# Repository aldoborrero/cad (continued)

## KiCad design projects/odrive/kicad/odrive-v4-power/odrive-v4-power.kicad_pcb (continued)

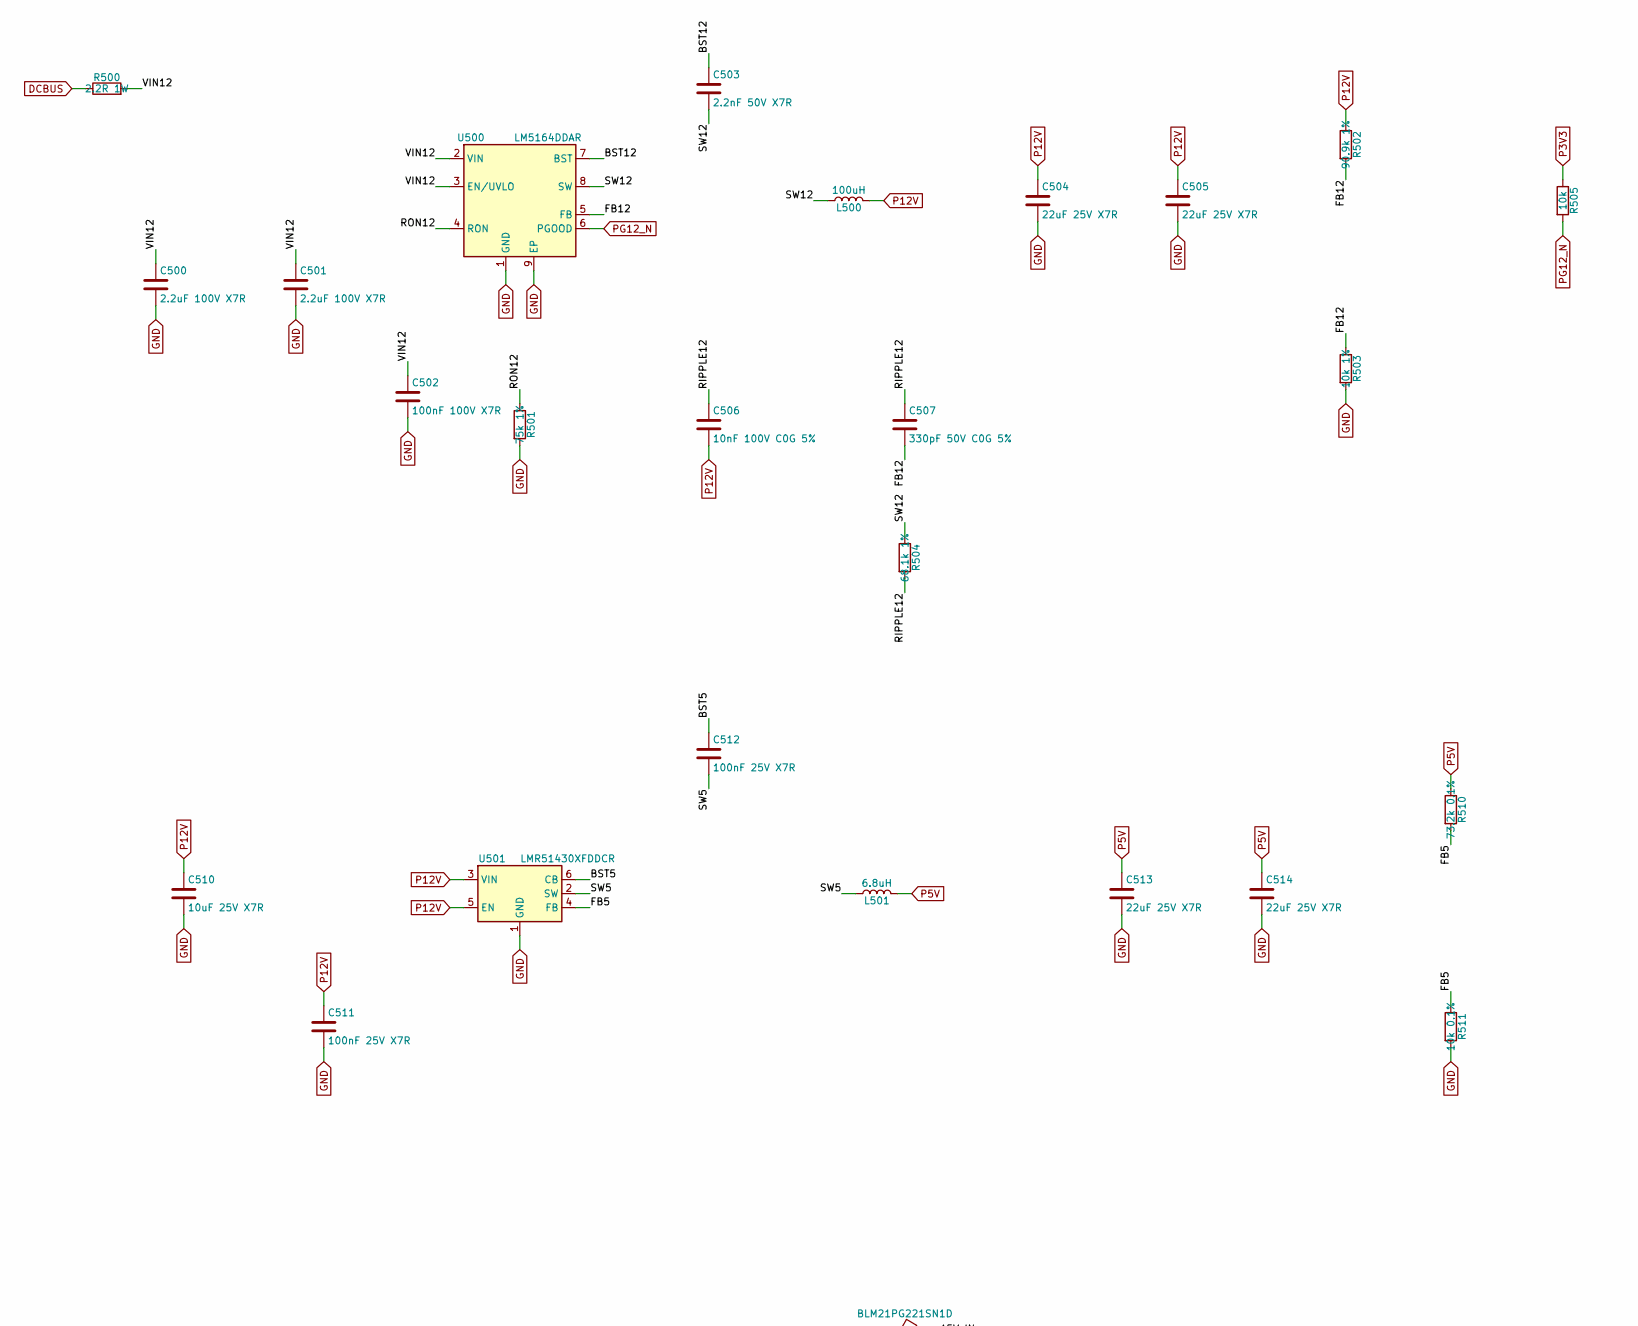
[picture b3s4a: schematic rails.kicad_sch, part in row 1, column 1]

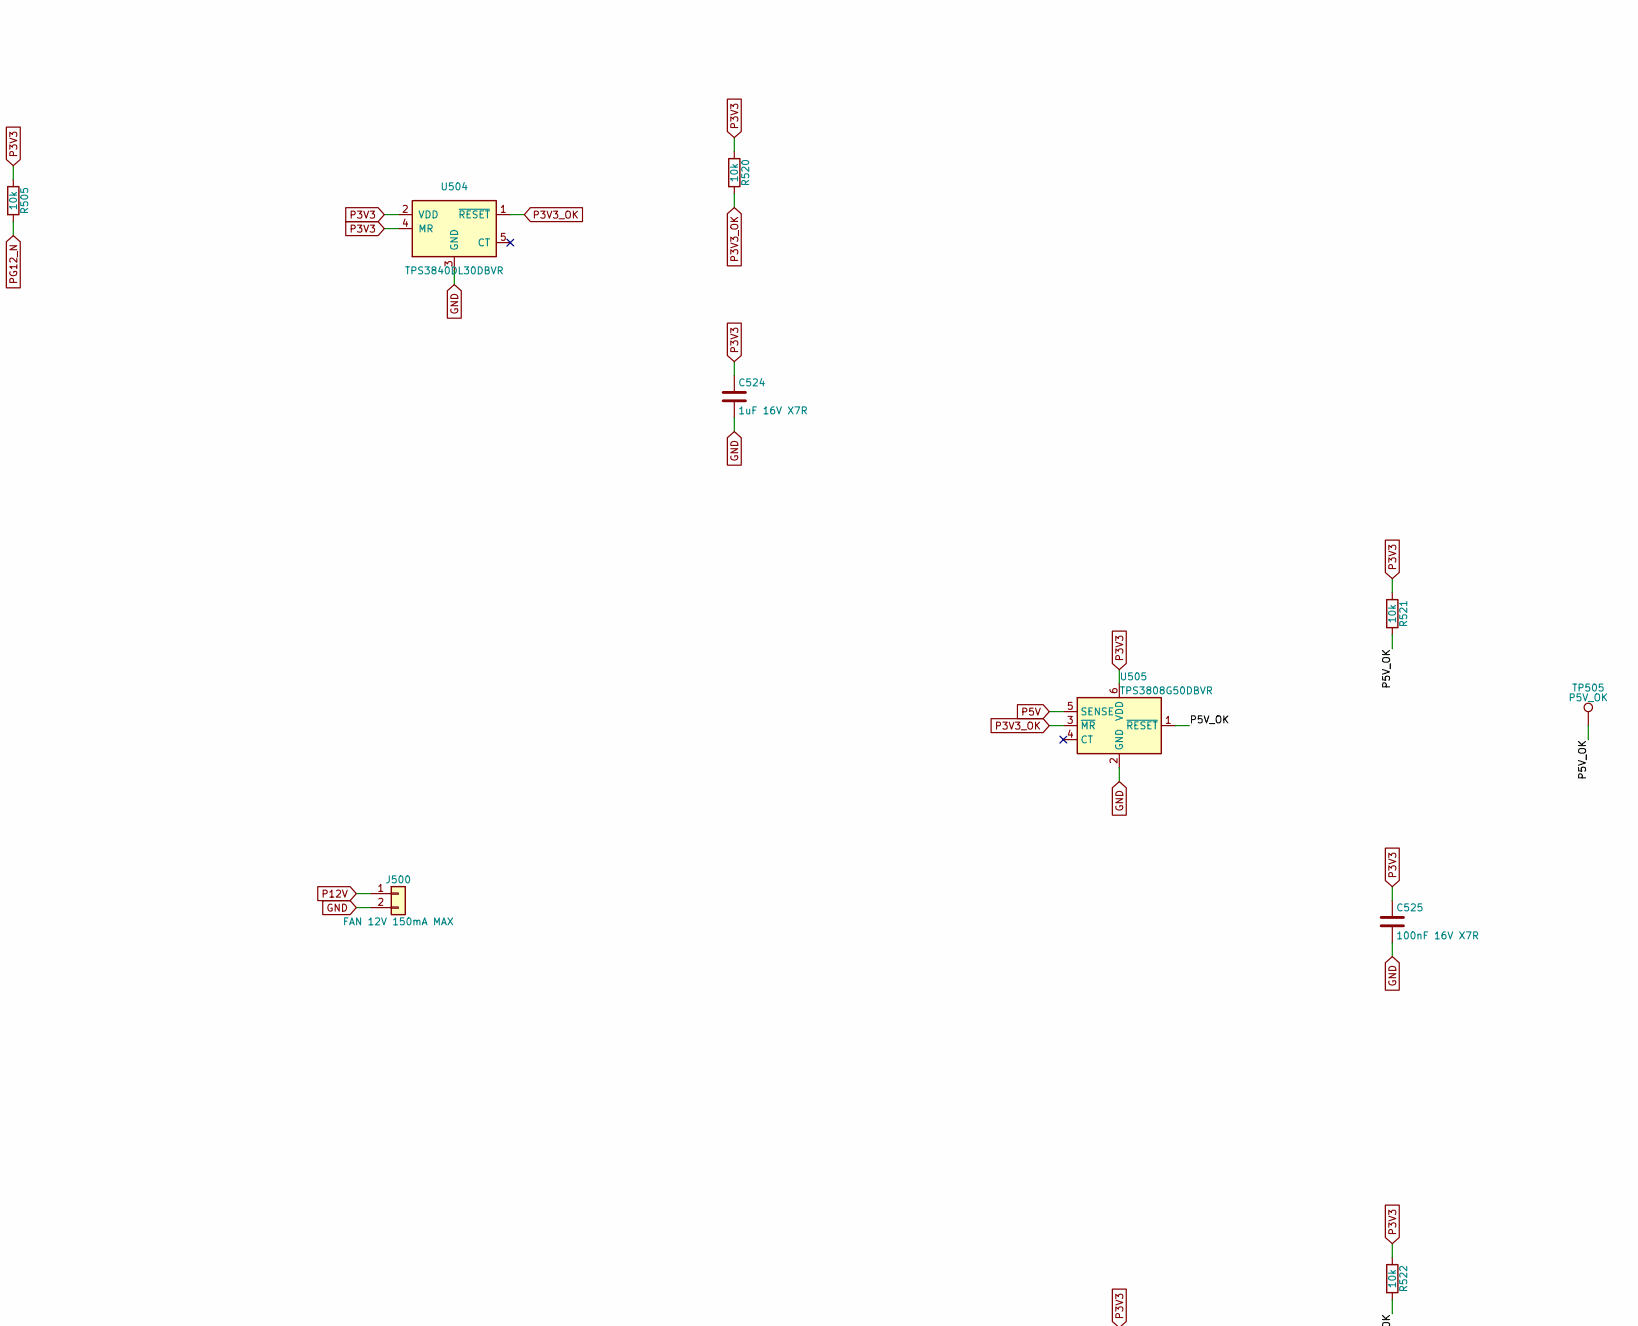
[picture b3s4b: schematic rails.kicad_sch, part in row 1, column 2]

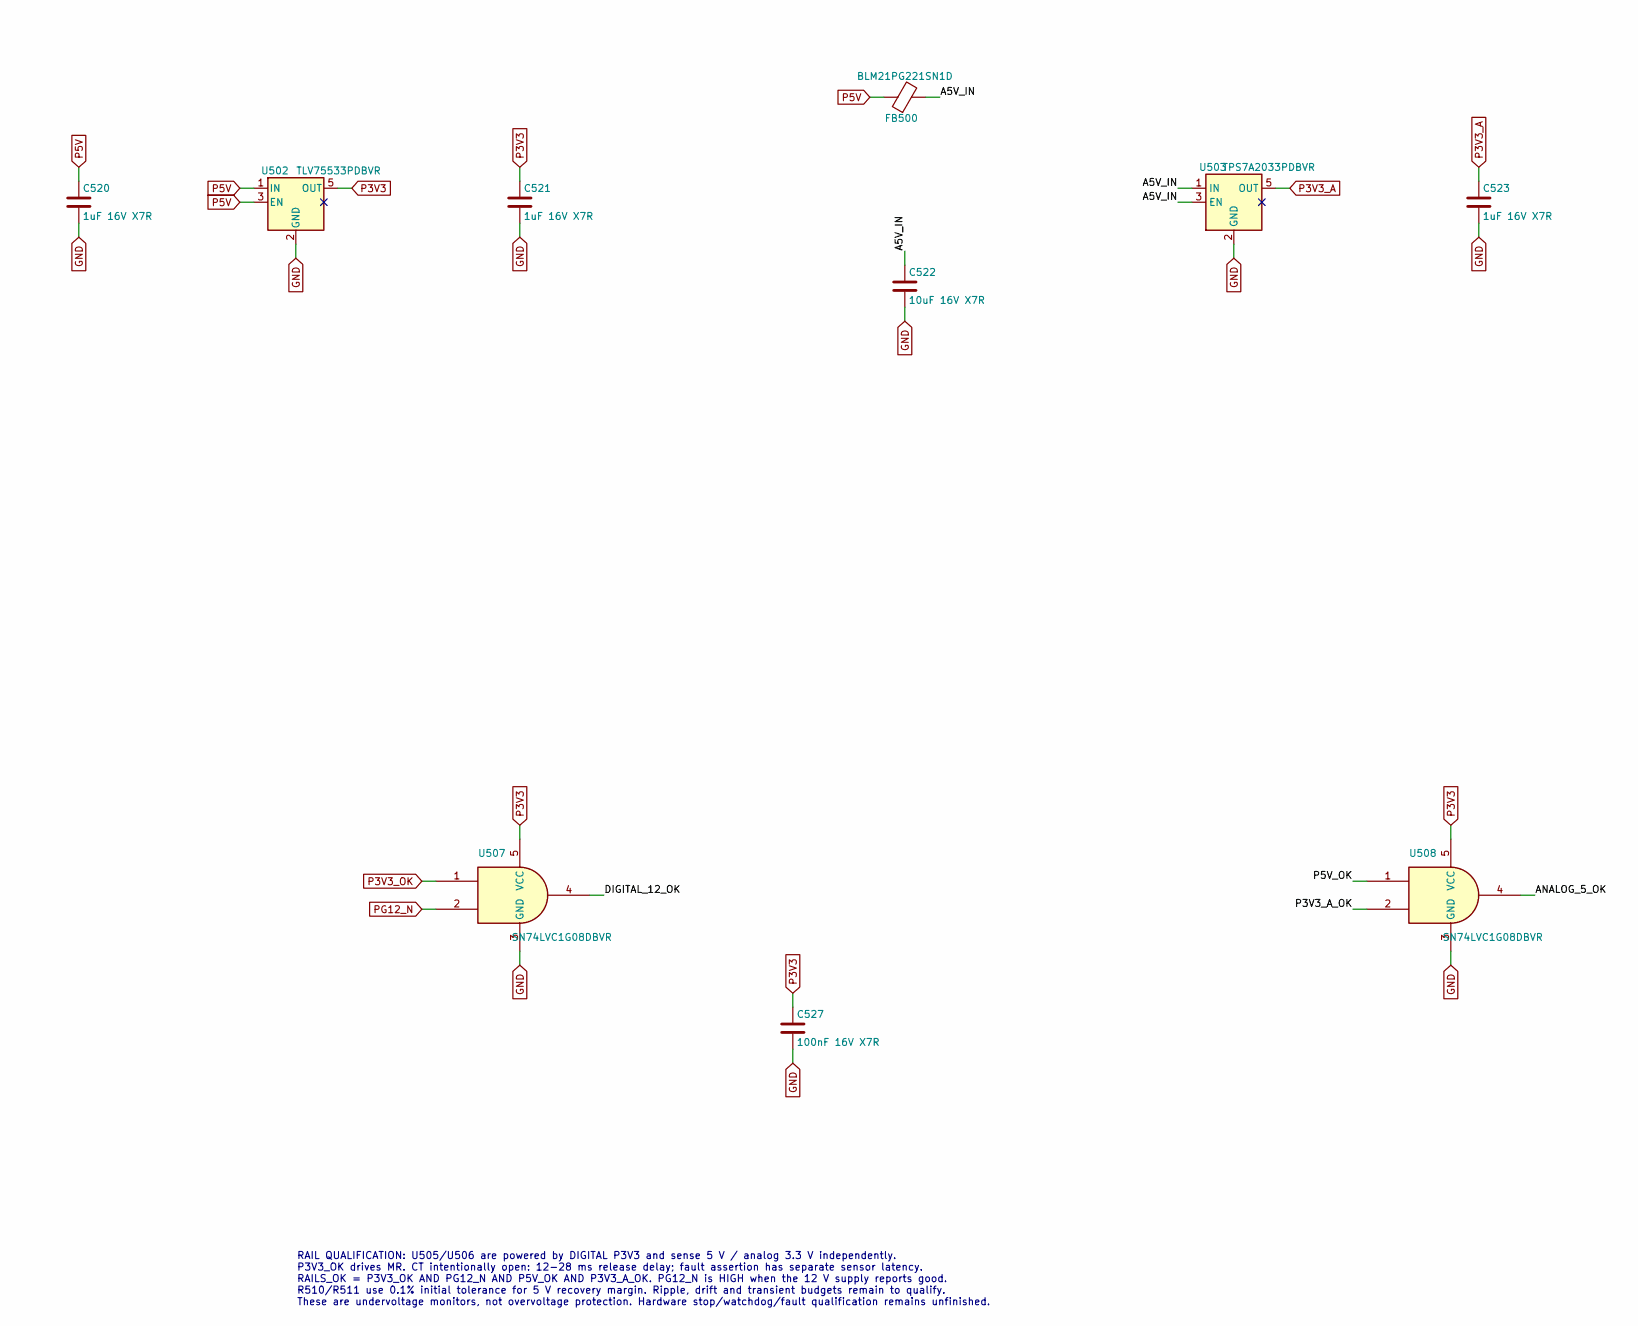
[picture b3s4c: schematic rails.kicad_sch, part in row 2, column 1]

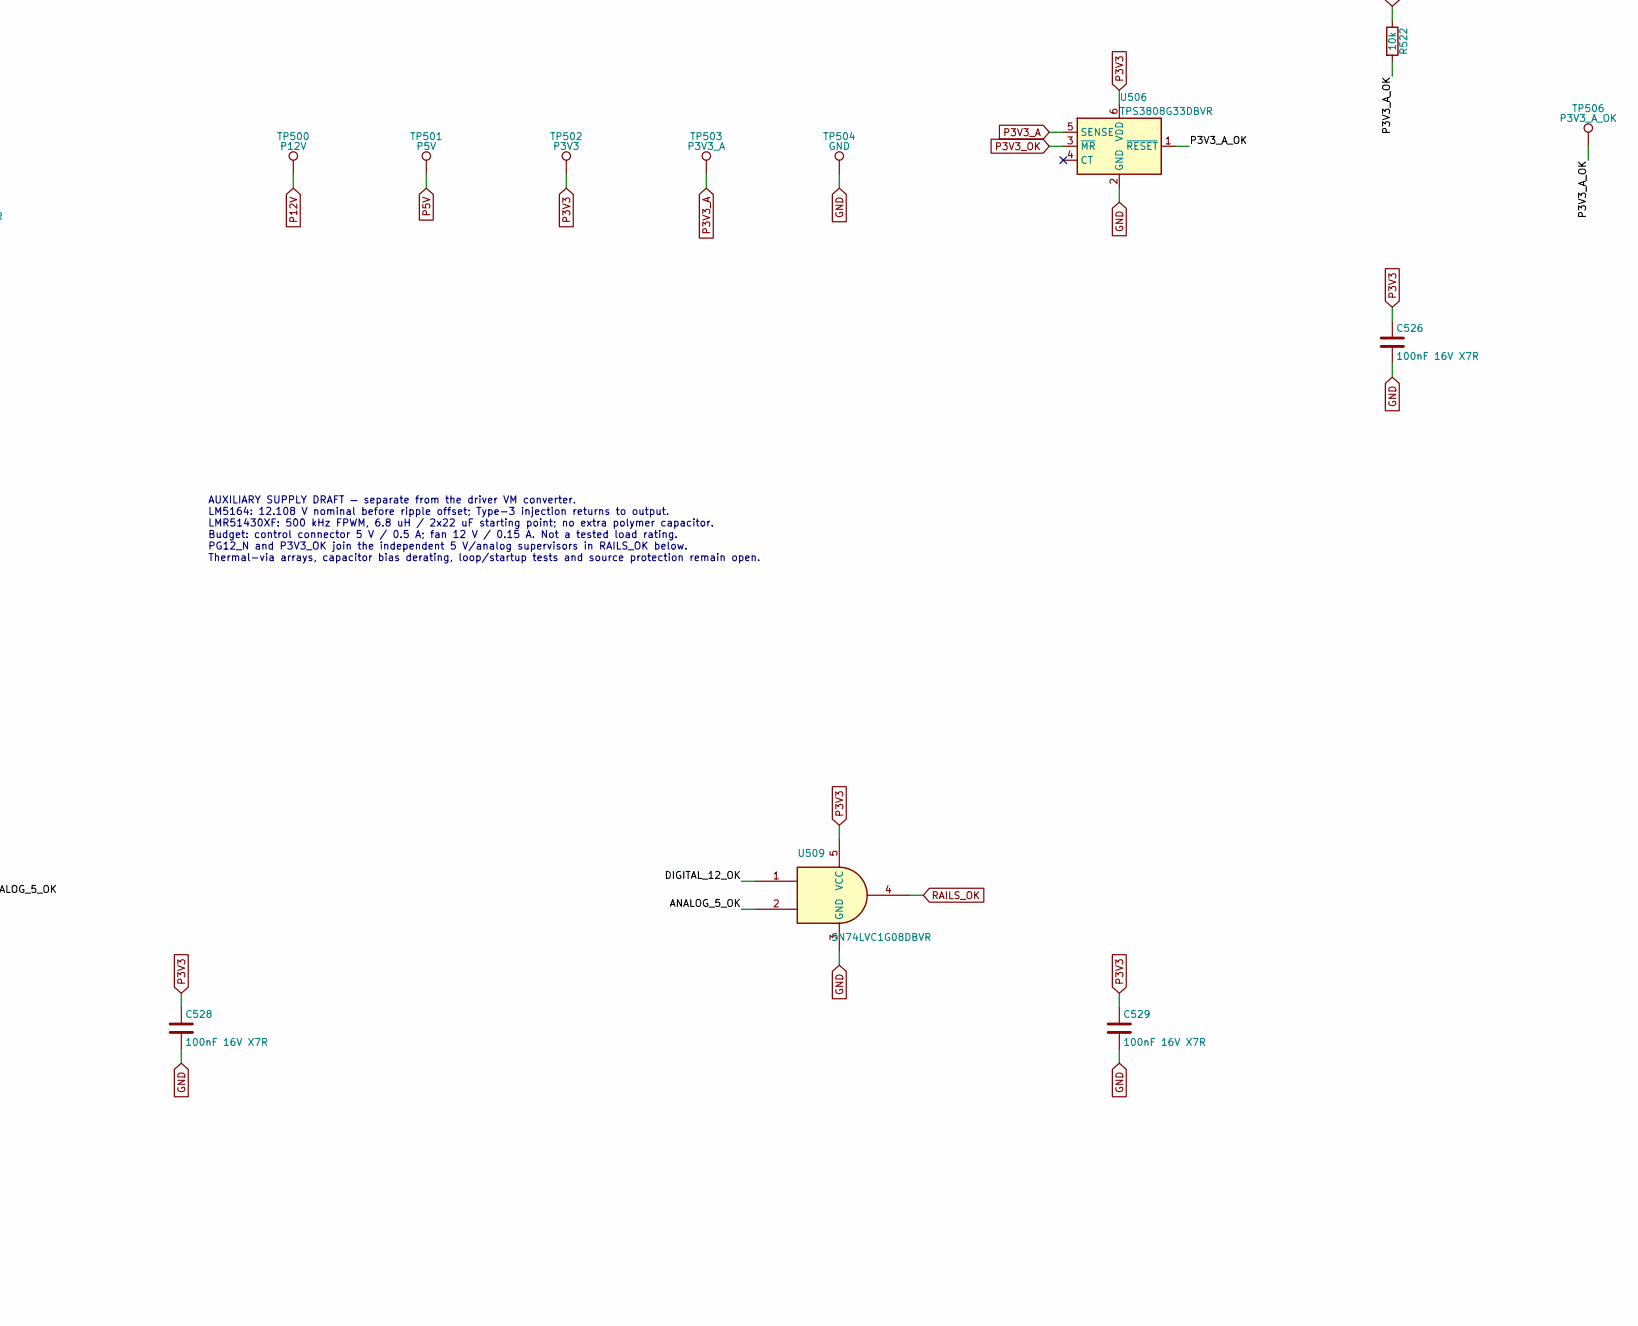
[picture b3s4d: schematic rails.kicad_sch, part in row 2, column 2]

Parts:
C500, C501: 2.2uF 100V X7R; C_1210_3225Metric
C502: 100nF 100V X7R; C_0603_1608Metric
C503: 2.2nF 50V X7R; C_0603_1608Metric
C504, C505, C513, C514: 22uF 25V X7R; C_1210_3225Metric
C506: 10nF 100V C0G 5%; C_0603_1608Metric
C507: 330pF 50V C0G 5%; C_0603_1608Metric
C510: 10uF 25V X7R; C_0805_2012Metric
C511, C512: 100nF 25V X7R; C_0603_1608Metric
C520, C521, C523, C524: 1uF 16V X7R; C_0603_1608Metric
C522: 10uF 16V X7R; C_0805_2012Metric
C525, C526, C527, C528, C529: 100nF 16V X7R; C_0603_1608Metric
FB500: BLM21PG221SN1D; L_0805_2012Metric
J500: FAN 12V 150mA MAX; PinHeader_1x02_P2.54mm_Vertical
L500: 100uH; L_Wuerth_WE-PD-Typ-LS
L501: 6.8uH; Coilcraft_XAL7070_682
R500: 2.2R 1W; R_2512_6332Metric
R501: 75k 1%; R_0603_1608Metric
R502: 90.9k 1%; R_0603_1608Metric
R503: 10k 1%; R_0603_1608Metric
R504: 68.1k 1%; R_0805_2012Metric
R505, R520, R521, R522: 10k; R_0603_1608Metric
R510: 73.2k 0.1%; R_0603_1608Metric
R511: 10k 0.1%; R_0603_1608Metric
TP500: P12V; TestPoint_Pad_D1.0mm
TP501: P5V; TestPoint_Pad_D1.0mm
TP502: P3V3; TestPoint_Pad_D1.0mm
TP503: P3V3_A; TestPoint_Pad_D1.0mm
TP504: GND; TestPoint_Pad_D1.0mm
TP505: P5V_OK; TestPoint_Pad_D1.0mm
TP506: P3V3_A_OK; TestPoint_Pad_D1.0mm
U500: LM5164DDAR; HSOP-8-1EP_3.9x4.9mm_P1.27mm_EP2.41x3.1mm
U501: LMR51430XFDDCR; TI_DDC0006A
U502: TLV75533PDBVR; SOT-23-5
U503: TPS7A2033PDBVR; SOT-23-5
U504: TPS3840DL30DBVR; SOT-23-5
U505: TPS3808G50DBVR; SOT-23-6
U506: TPS3808G33DBVR; SOT-23-6
U507, U508, U509: SN74LVC1G08DBVR; SOT-23-5

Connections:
/Auxiliary rails/A5V_IN: C522.1, FB500.2, U503.1 (IN), U503.3 (EN)
/Auxiliary rails/ANALOG_5_OK: U508.4, U509.2
/Auxiliary rails/BST5: C512.1, U501.6 (CB)
/Auxiliary rails/BST12: C503.1, U500.7 (BST)
/Auxiliary rails/DIGITAL_12_OK: U507.4, U509.1
/Auxiliary rails/FB5: R510.2, R511.1, U501.4 (FB)
/Auxiliary rails/FB12: C507.2, R502.2, R503.1, U500.5 (FB)
/Auxiliary rails/P3V3_A_OK: R522.2, TP506.1, U506.1 (~RESET), U508.2
/Auxiliary rails/P5V_OK: R521.2, TP505.1, U505.1 (~RESET), U508.1
/Auxiliary rails/RIPPLE12: C506.1, C507.1, R504.2
/Auxiliary rails/RON12: R501.1, U500.4 (RON)
/Auxiliary rails/SW5: C512.2, L501.1, U501.2 (SW)
/Auxiliary rails/SW12: C503.2, L500.1, R504.1, U500.8 (SW)
/Auxiliary rails/VIN12: C500.1, C501.1, C502.1, R500.2, U500.2 (VIN), U500.3 (EN/UVLO)
DCBUS: R500.1; also elsewhere on the board
GND: C500.2, C501.2, C502.2, C504.2, C505.2, C510.2, C511.2, C513.2, C514.2, C520.2, C521.2, C522.2, C523.2, C524.2, C525.2, C526.2, C527.2, C528.2, C529.2, J500.2, R501.2, R503.2, R511.2, TP504.1, U500.1 (GND), U500.9 (EP), U501.1 (GND), U502.2 (GND), U503.2 (GND), U504.3 (GND), U505.2 (GND), U506.2 (GND), U507.3 (GND), U508.3 (GND), U509.3 (GND); also elsewhere on the board
P3V3: C521.1, C524.1, C525.1, C526.1, C527.1, C528.1, C529.1, R505.1, R520.1, R521.1, R522.1, TP502.1, U502.5 (OUT), U504.2 (VDD), U504.4 (MR), U505.6 (VDD), U506.6 (VDD), U507.5 (VCC), U508.5 (VCC), U509.5 (VCC); also elsewhere on the board
P3V3_A: C523.1, TP503.1, U503.5 (OUT), U506.5 (SENSE); also elsewhere on the board
P3V3_OK: R520.2, U504.1 (~RESET), U505.3 (~MR), U506.3 (~MR), U507.1; also elsewhere on the board
P5V: C513.1, C514.1, C520.1, FB500.1, L501.2, R510.1, TP501.1, U502.1 (IN), U502.3 (EN), U505.5 (SENSE); also elsewhere on the board
P12V: C504.1, C505.1, C506.2, C510.1, C511.1, J500.1, L500.2, R502.1, TP500.1, U501.3 (VIN), U501.5 (EN)
PG12_N: R505.2, U500.6 (PGOOD), U507.2
RAILS_OK: U509.4; also elsewhere on the board

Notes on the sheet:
RAIL QUALIFICATION: U505/U506 are powered by DIGITAL P3V3 and sense 5 V / analog 3.3 V independently. P3V3_OK drives MR. CT intentionally open: 12-28 ms release delay; fault assertion has separate sensor latency. RAILS_OK = P3V3_OK AND PG12_N AND P5V_OK AND P3V3_A_OK. PG12_N is HIGH when the 12 V s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
AUXILIARY SUPPLY DRAFT — separate from the driver VM converter. LM5164: 12.108 V nominal before ripple offset; Type-3 injection returns to output. LMR51430XF: 500 kHz FPWM, 6.8 uH / 2x22 uF starting point; no extra polymer capacitor. Budget: control connector 5 V / 0.5 A; fan 12 V / 0.15 A. Not a t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

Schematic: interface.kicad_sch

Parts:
C600, C601, C602, C603, C604, C605, C610, C611, C612, C613, C614, C615, C616, C620, C621, C622, C623, C624, C625, C640, C642, C643, C644, C645, C646, C647, C648, C649, C650, C651, C652, C653, C654, C655, C656: 100nF 16V X7R; C_0603_1608Metric
C630, C631, C632, C641: 47pF 50V C0G 5%; C_0603_1608Metric
J600: STOP NC LOOP; PhoenixContact_MSTBA_2,5_2-G-5,08_1x02_P5.08mm_Horizontal
R600, R601, R602, R603, R604, R605, R610, R615, R617, R636, R650: 1k; R_0603_1608Metric
R611, R612, R613, R614, R616, R618, R619, R620, R621, R622, R623, R624, R625, R626, R627, R632, R635, R637, R638, R639, R640, R641, R651, R652, R659, R660, R661, R662, R663, R664, R676: 10k; R_0603_1608Metric
R630, R631, R633, R634: 220R 1%; R_0603_1608Metric
R653, R656: 100k 0.1%; R_0603_1608Metric
R654, R657, R671, R674: 976k 1%; R_0603_1608Metric
R655, R658: 182k 1%; R_0603_1608Metric
R670, R673: 169k 0.1%; R_0603_1608Metric
R672, R675: 102k 1%; R_0603_1608Metric
TP600: ARM_STORED; TestPoint_Pad_D1.0mm
TP601: MOTOR_PERMISSION; TestPoint_Pad_D1.0mm
TP602: DRV_ENABLE; TestPoint_Pad_D1.0mm
TP603: STOP_OK; TestPoint_Pad_D1.0mm
TP604: PRESENCE_OK; TestPoint_Pad_D1.0mm
TP605: WD_RECENT; TestPoint_Pad_D1.0mm
TP606: WD_OK; TestPoint_Pad_D1.0mm
U600, U601, U602, U603, U604, U605, U611, U612, U613, U615, U616, U623, U624, U625, U634, U635, U644: SN74LVC1G08DBVR; SOT-23-5
U610, U638, U639: SN74LVC1G74DCUR; TI_DCU0008A
U614, U620, U621, U622, U630: SN74LVC1G17DBVR; SOT-23-5
U631: LTC6993HS6-2#TRPBF; TSOT-23-6
U632: LTC6993HS6-4#TRPBF; TSOT-23-6
U633, U641, U643: SN74LVC1G32DBVR; SOT-23-5
U636: LTC6993HS6-1#TRPBF; TSOT-23-6
U637: LTC6993HS6-3#TRPBF; TSOT-23-6
U640, U642, U645: SN74LVC1G04DBVR; SOT-23-5

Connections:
/Interface and hardware interlocks/ARM_CORE_READY: R626.1, U615.1, U635.4
/Interface and hardware interlocks/ARM_FB_DRIVE: R617.1, R618.1, U614.4
/Interface and hardware interlocks/ARM_READY: R613.1, U610.6 (~CLR), U612.2, U615.4
/Interface and hardware interlocks/ARM_REQ: R610.2, R611.1, U610.1 (C), U611.2, U645.2
/Interface and hardware interlocks/ARM_REQUEST_HELD: U611.4, U612.1
/Interface and hardware interlocks/ARM_STORED: R619.1, TP600.1, U610.5 (Q), U611.1
/Interface and hardware interlocks/CTRL_ALIVE_OK: R640.1, U622.4, U624.2
/Interface and hardware interlocks/CTRL_ALIVE_SENSE: C632.1, R636.2, R637.1, U622.2
/Interface and hardware interlocks/DRV_WAKE_REQ: R615.2, R616.1, U613.1
/Interface and hardware interlocks/MOTOR_PERMISSION: R612.1, TP601.1, U600.2, U601.2, U602.2, U603.2, U604.2, U605.2, U612.4, U614.2
/Interface and hardware interlocks/PRESENCE_OK: R639.1, TP604.1, U621.4, U623.2
/Interface and hardware interlocks/PRESENCE_SENSE: C631.1, R634.2, R635.1, U621.2
/Interface and hardware interlocks/PWM_AH_IN: R600.2, R620.1, U600.1
/Interface and hardware interlocks/PWM_AL_IN: R601.2, R621.1, U601.1
/Interface and hardware interlocks/PWM_BH_IN: R602.2, R622.1, U602.1
/Interface and hardware interlocks/PWM_BL_IN: R603.2, R623.1, U603.1
/Interface and hardware interlocks/PWM_CH_IN: R604.2, R624.1, U604.1
/Interface and hardware interlocks/PWM_CL_IN: R605.2, R625.1, U605.1
/Interface and hardware interlocks/STOP_OK: R638.1, TP603.1, U620.4, U623.1
/Interface and hardware interlocks/STOP_PRESENCE_OK: U623.4, U624.1
/Interface and hardware interlocks/STOP_RETURN: J600.2, R631.1
/Interface and hardware interlocks/STOP_SEND: J600.1, R630.2
/Interface and hardware interlocks/STOP_SENSE: C630.1, R631.2, R632.1, U620.2
/Interface and hardware interlocks/WAKE_CONDITIONS_OK: R627.1, U625.4, U644.1
/Interface and hardware interlocks/WAKE_READY: R614.1, U613.2, U616.4
/Interface and hardware interlocks/WAKE_WITH_WD: U616.2, U644.4
/Interface and hardware interlocks/WD_EARLY: U641.4, U642.2
/Interface and hardware interlocks/WD_EARLY_FALL: R664.1, U639.5 (Q), U641.2
/Interface and hardware interlocks/WD_EARLY_FALL_T_DIV: R674.2, R675.1, U637.4 (DIV)
/Interface and hardware interlocks/WD_EARLY_FALL_T_SET: R673.1, U637.3 (SET)
/Interface and hardware interlocks/WD_EARLY_RISE: R663.1, U638.5 (Q), U641.1
/Interface and hardware interlocks/WD_EARLY_RISE_T_DIV: R671.2, R672.1, U636.4 (DIV)
/Interface and hardware interlocks/WD_EARLY_RISE_T_SET: R670.1, U636.3 (SET)
/Interface and hardware interlocks/WD_FALL_ACTIVE: U632.6 (OUT), U633.2
/Interface and hardware interlocks/WD_INV: U639.1 (C), U640.4
/Interface and hardware interlocks/WD_LATE_FALL_DIV: R657.2, R658.1, U632.4 (DIV)
/Interface and hardware interlocks/WD_LATE_FALL_SET: R656.1, U632.3 (SET)
/Interface and hardware interlocks/WD_LATE_RISE_DIV: R654.2, R655.1, U631.4 (DIV)
/Interface and hardware interlocks/WD_LATE_RISE_SET: R653.1, U631.3 (SET)
/Interface and hardware interlocks/WD_LOCAL: R652.1, U630.4, U631.1 (TRIG), U632.1 (TRIG), U636.1 (TRIG), U637.1 (TRIG), U638.1 (C), U640.2
/Interface and hardware interlocks/WD_RECENT: R660.1, TP605.1, U633.4, U634.1
/Interface and hardware interlocks/WD_RISE_ACTIVE: U631.6 (OUT), U633.1
/Interface and hardware interlocks/WD_SENSE: C641.1, R650.2, R651.1, U630.2
/Interface and hardware interlocks/WD_SHORT_FALL: U637.6 (OUT), U638.2 (D)
/Interface and hardware interlocks/WD_SHORT_RISE: U636.6 (OUT), U639.2 (D)
/Interface and hardware interlocks/WD_WINDOW_OK: R659.1, U634.2, U642.4
ARM_FAULTS_OK: R662.1, U635.2; also elsewhere on the board
ARM_FB: R617.2; also elsewhere on the board
ARM_NOT_REQ: U643.1, U645.4; also elsewhere on the board
C_ARM_REQ: R610.1; also elsewhere on the board
C_CTRL_ALIVE: R636.1; also elsewhere on the board
C_DRV_WAKE_REQ: R615.1; also elsewhere on the board
C_PWM_AH: R600.1; also elsewhere on the board
C_PWM_AL: R601.1; also elsewhere on the board
C_PWM_BH: R602.1; also elsewhere on the board
C_PWM_BL: R603.1; also elsewhere on the board
C_PWM_CH: R604.1; also elsewhere on the board
C_PWM_CL: R605.1; also elsewhere on the board
C_WD_KICK: R650.1; also elsewhere on the board
DRV_ENABLE: TP602.1, U613.4, U615.2; also elsewhere on the board
GND: C600.2, C601.2, C602.2, C603.2, C604.2, C605.2, C610.2, C611.2, C612.2, C613.2, C614.2, C615.2, C616.2, C620.2, C621.2, C622.2, C623.2, C624.2, C625.2, C630.2, C631.2, C632.2, C640.2, C641.2, C642.2, C643.2, C644.2, C645.2, C646.2, C647.2, C648.2, C649.2, C650.2, C651.2, C652.2, C653.2, C654.2, C655.2, C656.2, R611.2, R612.2, R613.2, R614.2, R616.2, R618.2, R619.2, R620.2, R621.2, R622.2, R623.2, R624.2, R625.2, R626.2, R627.2, R632.2, R635.2, R637.2, R638.2, R639.2, R640.2, R641.2, R651.2, R652.2, R653.2, R655.2, R656.2, R658.2, R659.2, R660.2, R661.2, R662.2, R663.2, R664.2, R670.2, R672.2, R673.2, R675.2, R676.2, U600.3 (GND), U601.3 (GND), U602.3 (GND), U603.3 (GND), U604.3 (GND), U605.3 (GND), U610.4 (GND), U611.3 (GND), U612.3 (GND), U613.3 (GND), U614.3 (GND), U615.3 (GND), U616.3 (GND), U620.3 (GND), U621.3 (GND), U622.3 (GND), U623.3 (GND), U624.3 (GND), U625.3 (GND), U630.3 (GND), U631.2 (GND), U632.2 (GND), U633.3 (GND), U634.3 (GND), U635.3 (GND), U636.2 (GND), U637.2 (GND), U638.4 (GND), U639.4 (GND), U640.3 (GND), U641.3 (GND), U642.3 (GND), U643.3 (GND), U644.3 (GND), U645.3 (GND); also elsewhere on the board
LINK_OK: U624.4, U625.1; also elsewhere on the board
P3V3: C600.1, C601.1, C602.1, C603.1, C604.1, C605.1, C610.1, C611.1, C612.1, C613.1, C614.1, C615.1, C616.1, C620.1, C621.1, C622.1, C623.1, C624.1, C625.1, C640.1, C642.1, C643.1, C644.1, C645.1, C646.1, C647.1, C648.1, C649.1, C650.1, C651.1, C652.1, C653.1, C654.1, C655.1, C656.1, R630.1, R633.1, R654.1, R657.1, R671.1, R674.1, U600.5 (VCC), U601.5 (VCC), U602.5 (VCC), U603.5 (VCC), U604.5 (VCC), U605.5 (VCC), U610.2 (D), U610.7 (~PRE), U610.8 (VCC), U611.5 (VCC), U612.5 (VCC), U613.5 (VCC), U614.5 (VCC), U615.5 (VCC), U616.5 (VCC), U620.5 (VCC), U621.5 (VCC), U622.5 (VCC), U623.5 (VCC), U624.5 (VCC), U625.5 (VCC), U630.5 (VCC), U631.5 (V+), U632.5 (V+), U633.5 (VCC), U634.5 (VCC), U635.5 (VCC), U636.5 (V+), U637.5 (V+), U638.7 (~PRE), U638.8 (VCC), U639.7 (~PRE), U639.8 (VCC), U640.5 (VCC), U641.5 (VCC), U642.5 (VCC), U643.5 (VCC), U644.5 (VCC), U645.5 (VCC); also elsewhere on the board
P3V3_OK: U638.6 (~CLR), U639.6 (~CLR); also elsewhere on the board
POWER_INTERFACE_OK: U616.1; also elsewhere on the board
PRESENCE_OUT: R633.2; also elsewhere on the board
PRESENCE_RETURN: R634.1; also elsewhere on the board
P_PWM_AH: U600.4; also elsewhere on the board
P_PWM_AL: U601.4; also elsewhere on the board
P_PWM_BH: U602.4; also elsewhere on the board
P_PWM_BL: U603.4; also elsewhere on the board
P_PWM_CH: U604.4; also elsewhere on the board
P_PWM_CL: U605.4; also elsewhere on the board
WAKE_FAULTS_OK: R641.1, U625.2; also elsewhere on the board
WD_OK: R661.1, TP606.1, U634.4, U635.1, U643.2; also elsewhere on the board
WD_WAKE_OK: R676.1, U643.4, U644.2; also elsewhere on the board

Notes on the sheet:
STOP/PRESENCE DRAFT: loop powered only by P3V3; external NC stop contact returns STOP_SEND to STOP_RETURN. No external voltage. Main connector presence requires a passive link on C between PRESENCE_OUT and PRESENCE_RETURN. Open loop disarms. CTRL_ALIVE must come from supervised controller reset/pow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
WATCHDOG DRAFT: both transition polarities count. U631/U632 give 128 us nominal retriggerable coverage; U633 ORs them. U636/U637 generate 27.04 us short windows. Each detector flip-flop samples the opposite-edge window. WD_OK requires recent activity and no early-edge indication. Accepted interval 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
INCOMPLETE INTERLOCK: ARM_FAULTS_OK and WAKE_FAULTS_OK now come from the retained-fault sheet; raw protection sources remain pending. No bridging these signals for normal operation. Main connector and brake/OC/OV/thermal qualification remain pending. Retained acknowledgement is on faults.kicad_sch.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
WAKE_READY = RAILS_OK AND WAKE_CONDITIONS_OK AND (NOT ARM_REQ OR WD_OK). A watchdog fault during ARM_REQ removes both driver ENABLE and PWM permission. ARM_REQ low permits diagnostic/configuration wake. WAKE_CONDITIONS_OK = STOP_OK AND PRESENCE_OK AND CTRL_ALIVE_OK AND WAKE_FAULTS_OK from the retai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
